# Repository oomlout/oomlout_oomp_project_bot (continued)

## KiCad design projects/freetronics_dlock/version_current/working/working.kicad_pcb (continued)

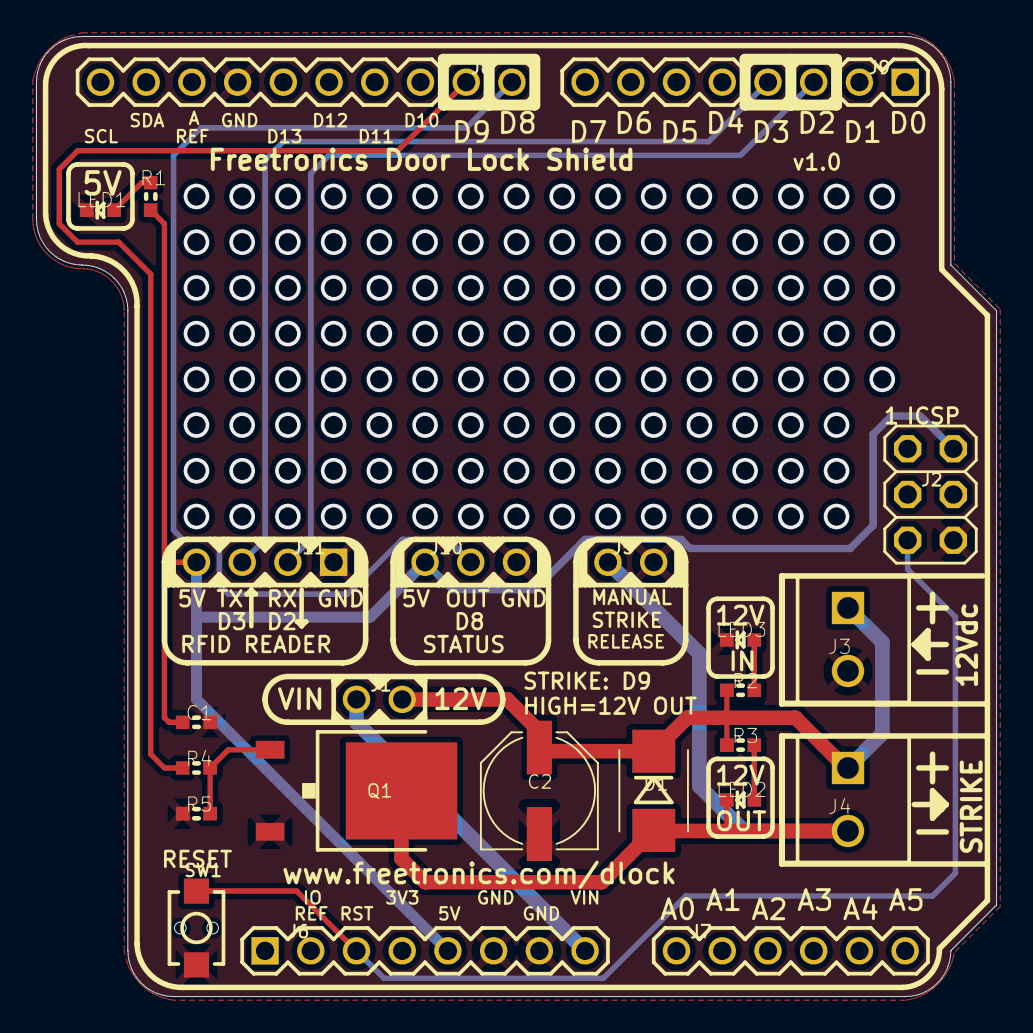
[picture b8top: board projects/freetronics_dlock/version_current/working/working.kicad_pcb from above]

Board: 2 copper layers, 53.3 x 53.3 mm, 24 parts (0 on the bottom side), 14 nets.

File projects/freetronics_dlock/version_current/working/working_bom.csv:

"Id";"Designator";"Footprint";"Quantity";"Designation";"Supplier and ref";
1;"J8";"1X10";1;"M100.1";;;
2;"J11";"1X04";1;"";;;
3;"J2";"2X03";1;"ICSP";;;
4;"J3";"SCREWTERMINAL-3.5MM-2";1;"12Vdc IN";;;
5;"Q1";"DPACK";1;"NTD5867NLT4G";;;
6;"J4";"SCREWTERMINAL-3.5MM-2";1;"STRIKE";;;
7;"J6,J9";"1X08";2;"Digital_0_7";;;
8;"J1";"1X02";1;"";;;
9;"C1";"0603";1;"100nF";;;
10;"SW1";"TACTILE_SWITCH_SMD_2PIN_TINY";1;"TAC_SWITCH_2PIN";;;
11;"R5";"0603";1;"10K";;;
12;"R4";"0603";1;"1K";;;
13;"LED2";"LED-0603";1;"RED";;;
14;"D1";"SMB-DIODE";1;"1N4004 SMB";;;
15;"R3,R1,R2";"0603";3;"2K2";;;
16;"C2";"PANASONIC_D";1;"47uF 25V";;;
17;"LED1";"LED-0603";1;"BLUE";;;
18;"LED3";"LED-0603";1;"GREEN";;;
19;"J10";"1X03";1;"";;;
20;"J7";"1X06";1;"Analog";;;
21;"J5";"1X02";1;"RELEASE";;;
